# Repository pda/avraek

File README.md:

ADB Apple Desktop Bus keyboard adapter
======================================

Aims to use a cheap microcontroller to expose an Apple Extended Keyboard II
as a USB keyboard.

Hardware
--------

Single ADB data line connects to bottom-left pin of keyboard Mini-DIN with 1K pull-up resistor.

ATtiny328p (Arduino Uno)
------------------------

Defaults ADB to `PORTB` bit `0` which is ATmega328p pin 14, and Arduino digital
pin 8. See `Makefile` to override this using environment variables.

```sh
make clean all burn
```

ATtiny85
--------

Set to internal 16.5 MHz frequency like http://www.obdev.at/products/vusb/easylogger.html

```
# Fuse high byte:
# 0xdd = 1 1 0 1   1 1 0 1
#        ^ ^ ^ ^   ^ \-+-/ 
#        | | | |   |   +------ BODLEVEL 2..0 (brownout trigger level -> 2.7V)
#        | | | |   +---------- EESAVE (preserve EEPROM on Chip Erase -> not preserved)
#        | | | +-------------- WDTON (watchdog timer always on -> disable)
#        | | +---------------- SPIEN (enable serial programming -> enabled)
#        | +------------------ DWEN (debug wire enable)
#        +-------------------- RSTDISBL (disable external reset -> enabled)
#
# Fuse low byte:
# 0xe1 = 1 1 1 0   0 0 0 1
#        ^ ^ \+/   \--+--/
#        | |  |       +------- CKSEL 3..0 (clock selection -> HF PLL)
#        | |  +--------------- SUT 1..0 (BOD enabled, fast rising power)
#        | +------------------ CKOUT (clock output on CKOUT pin -> disabled)
#        +-------------------- CKDIV8 (divide clock by 8 -> don't divide)
```

```sh
avrdude -p attiny85 -c usbtiny -U hfuse:w:0xdd:m -U lfuse:w:0xe1:m
```

Build the code, use `PORTB` bit `3` which is ATtiny85 pin 2:

```sh
MCU=attiny85 F_CPU=16500000 ISP_PROGRAMMER=usbtiny ADB_PORT_BIT=3 make clean all burn
```

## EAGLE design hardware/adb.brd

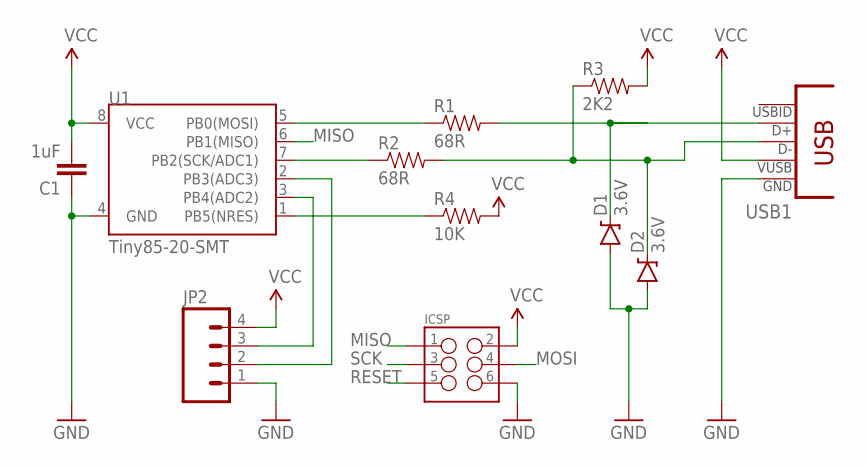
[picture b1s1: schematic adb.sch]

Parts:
C1: 1uF; 0805
D1, D2: 3.6V; SOD-323
ICSP: M03X22X3_SILK_SM; 2X3
JP2: M04PTH; 1X04
R1, R2: 68R; 0805
R3: 2K2; 0805
R4: 10K; 0805
U1: Tiny85-20-SMT; SO08-EIAJ
USB1: CON-USB-F-MICRO-B; CONN_USB_MICRO-B

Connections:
D+: D1.C, R1.2, USB1.P3 (D+)
D-: D2.C, R2.2, R3.1, USB1.P2 (D-)
GND: C1.1, D1.A, D2.A, ICSP.6, JP2.1, U1.4 (GND), USB1.P5 (GND)
MISO: ICSP.1, U1.6 (PB1(MISO))
MOSI: ICSP.4, R1.1, U1.5 (PB0(MOSI))
unnamed: JP2.3, U1.3 (PB4(ADC2))
unnamed: JP2.2, U1.2 (PB3(ADC3))
RESET: ICSP.5, R4.1, U1.1 (PB5(NRES))
SCK: ICSP.3, R2.1, U1.7 (PB2(SCK/ADC1))
VCC: C1.2, ICSP.2, JP2.4, R3.2, R4.2, U1.8 (VCC), USB1.P1 (VUSB)

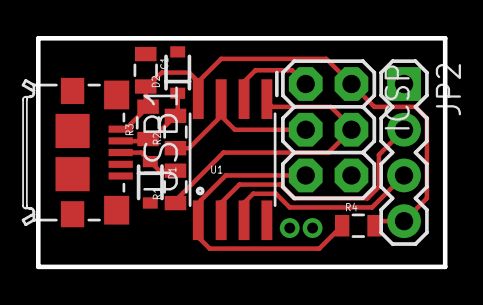
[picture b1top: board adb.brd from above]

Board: 2 copper layers, 22.6 x 12.7 mm, 11 parts (0 on the bottom side), 10 nets.

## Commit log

2015-02-28 main.c: blink PORTB. Requires F_CPU define.
2015-02-28 Makefile: builds and burns main.hex from main.c
2015-03-01 Makefile: USB port change.
2015-03-01 main.c: send 3ms reset pulse to ADB bus.
2015-03-01 main.c: initialize keyboard address; address 3 talk reg 3.
    Response ignored, but has been observed via logic analyzer:
    101100011000000100
    1 = start bit
    01100011 = byte 0 (low four bits vary)
    00000010 = byte 1
    0 = stop bit
2015-03-01 struct adb_cmd encapsulates address, command, register.
2015-03-01 adb.c + adb.h extracted from main.c
2015-03-01 PORTB, DDRB and pin 0 refs moved from adb.{c,h} to Makefile.
2015-03-01 avr-uart submodule.
2015-03-01 avr-uart integrated; status output.
2015-03-02 main.c: stream stdout to uart0 for printf.
2015-03-02 adb_read16() to read response from keyboard.
2015-03-02 Renames; adb_write*() functions.
2015-03-02 Animate keyboard LEDs on start-up.
2015-03-02 adb_reset: wait 100ms + 200ms during reset.
    Otherwise some resets, especially during power-up, are unsuccessful.
2015-03-02 Remove unused uart printf()
2015-03-02 adb_send_byte() was adb_write8()
2015-03-02 adb_send_low/adb_send_high were adb_write_low/adb_write_high
2015-03-02 adb_command_data_16 was adb_write16
2015-03-02 adb_receive_16 was adb_read16.
2015-03-02 adb: sort functions; public/private, alphabetic.
2015-03-04 Compile flags for ADB_PORT, ADB_PORT_PIN overhauled.
2015-03-04 Makefile overhaul.
2015-03-04 adb_keyboard_initialize was initialize_adb_keyboard.
2015-03-04 Raw key codes (register 0) logged to UART0 every 500ms.
2015-03-04 adb_keyboard.c extracted from adb.c
2015-03-04 struct adb_response_16, represents timed_out (no key presses).
2015-03-04 print key transitions to UART0 e.g. "up: 1F (31)"
2015-03-06 UART / printf support deleted; attiny85 incompatible.
2015-03-06 ATtiny85 compatibility; make requires MCU, F_CPU, ISP_PORT etc.
2015-03-06 README.md with some hardware/build/fuse notes.
2015-03-15 hardware: AVR reset pulled high.
2015-03-15 usbdrv vendored; HID descriptor; appears on USB host.
    * Successfully appears on the host computer USB device list.
    * Uses PB1 to connect/disconnect USB via D- pull-up resistor.
    * Not currently on schematic.
    * Will attempt to do away with this.
2015-03-15 hardware: adb.brd and adb.sch; work in progress.
2015-03-15 hardware: DRU from SparkFun not OSHPark
2015-03-15 hardware: polish; silk screen text etc.
2015-03-15 hardware: rounded corners; silk tweaks.
2015-03-15 hardware: tweaks; Eagle 7.2 upgrade.
2015-03-15 hardware: bumped ICSP up, rearranged Rs and Ds.
2015-03-15 hardware/.gitignore: ignore gerbers produced by OSHPark CAM.
2015-03-15 Gerbv (Gerber Viewer) project file.
2015-03-15 WIP: ADB key presses send USB key presses, but all wrong.
2015-03-15 adb_receive_16() explicitly clears response->timed_out.
2015-03-15 usbconfig.h: USB_CFG_MAX_BUS_POWER 200 mA
2015-03-15 usbconfig.h: disable USB_CFG_PULLUP; pull-up hard-wired to VCC.
2015-03-15 keybuffer: map up/down events into circular list of pressed keys.
2015-03-15 keybuffer integrated into main.c
2015-03-16 keymap.rb: generates keymap and key name constants.
    Example:
    ./keymap.rb keymap > keymap.h
    ./keymap.rb keys > aek2_keys.h
2015-03-16 aek2_keys.h: ADB keycode constants; manually collated.
2015-03-16 keymap.h generated by keymap.rb
2015-03-17 keymap fixes; FSLASH, GRAVE, CAPS.
2015-03-17 Support modifier keys; CTRL, SHIFT, OPTION, CMD.
2015-03-17 usbSetInterrupt() once per ADB response, not per transition.
    ADB responses contain one or two transitions, but there's no point
    setting USB interrupt for each of them.
2015-03-17 *_private.h eliminated; integrated into *.c files.
2015-03-17 adb.c open-drain; pulls low, releases to hi-Z for high.
    ADB circuit includes external pull-up resistor.
2015-03-17 adb_keyboard tidied; use constants, remove unused include.
2015-03-17 test_keybuffer.c has build/usage instructions.
2015-03-17 keybuffer.c tidied; section heading comments.
2015-03-17 usb_keyboard.c crudely extracted from main.c
2015-03-17 main.c unused includes removed.
2015-03-17 main.c simplified; adb/usb initialization details extracted.
2015-03-19 Calibrate oscillator using V-USB osccal code.

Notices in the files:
parts and their libraries:
SparkFun-Capacitors: Licensing: Creative Commons ShareAlike 4.0 International - https://creativecommons.org/licenses/by-sa/4.0
